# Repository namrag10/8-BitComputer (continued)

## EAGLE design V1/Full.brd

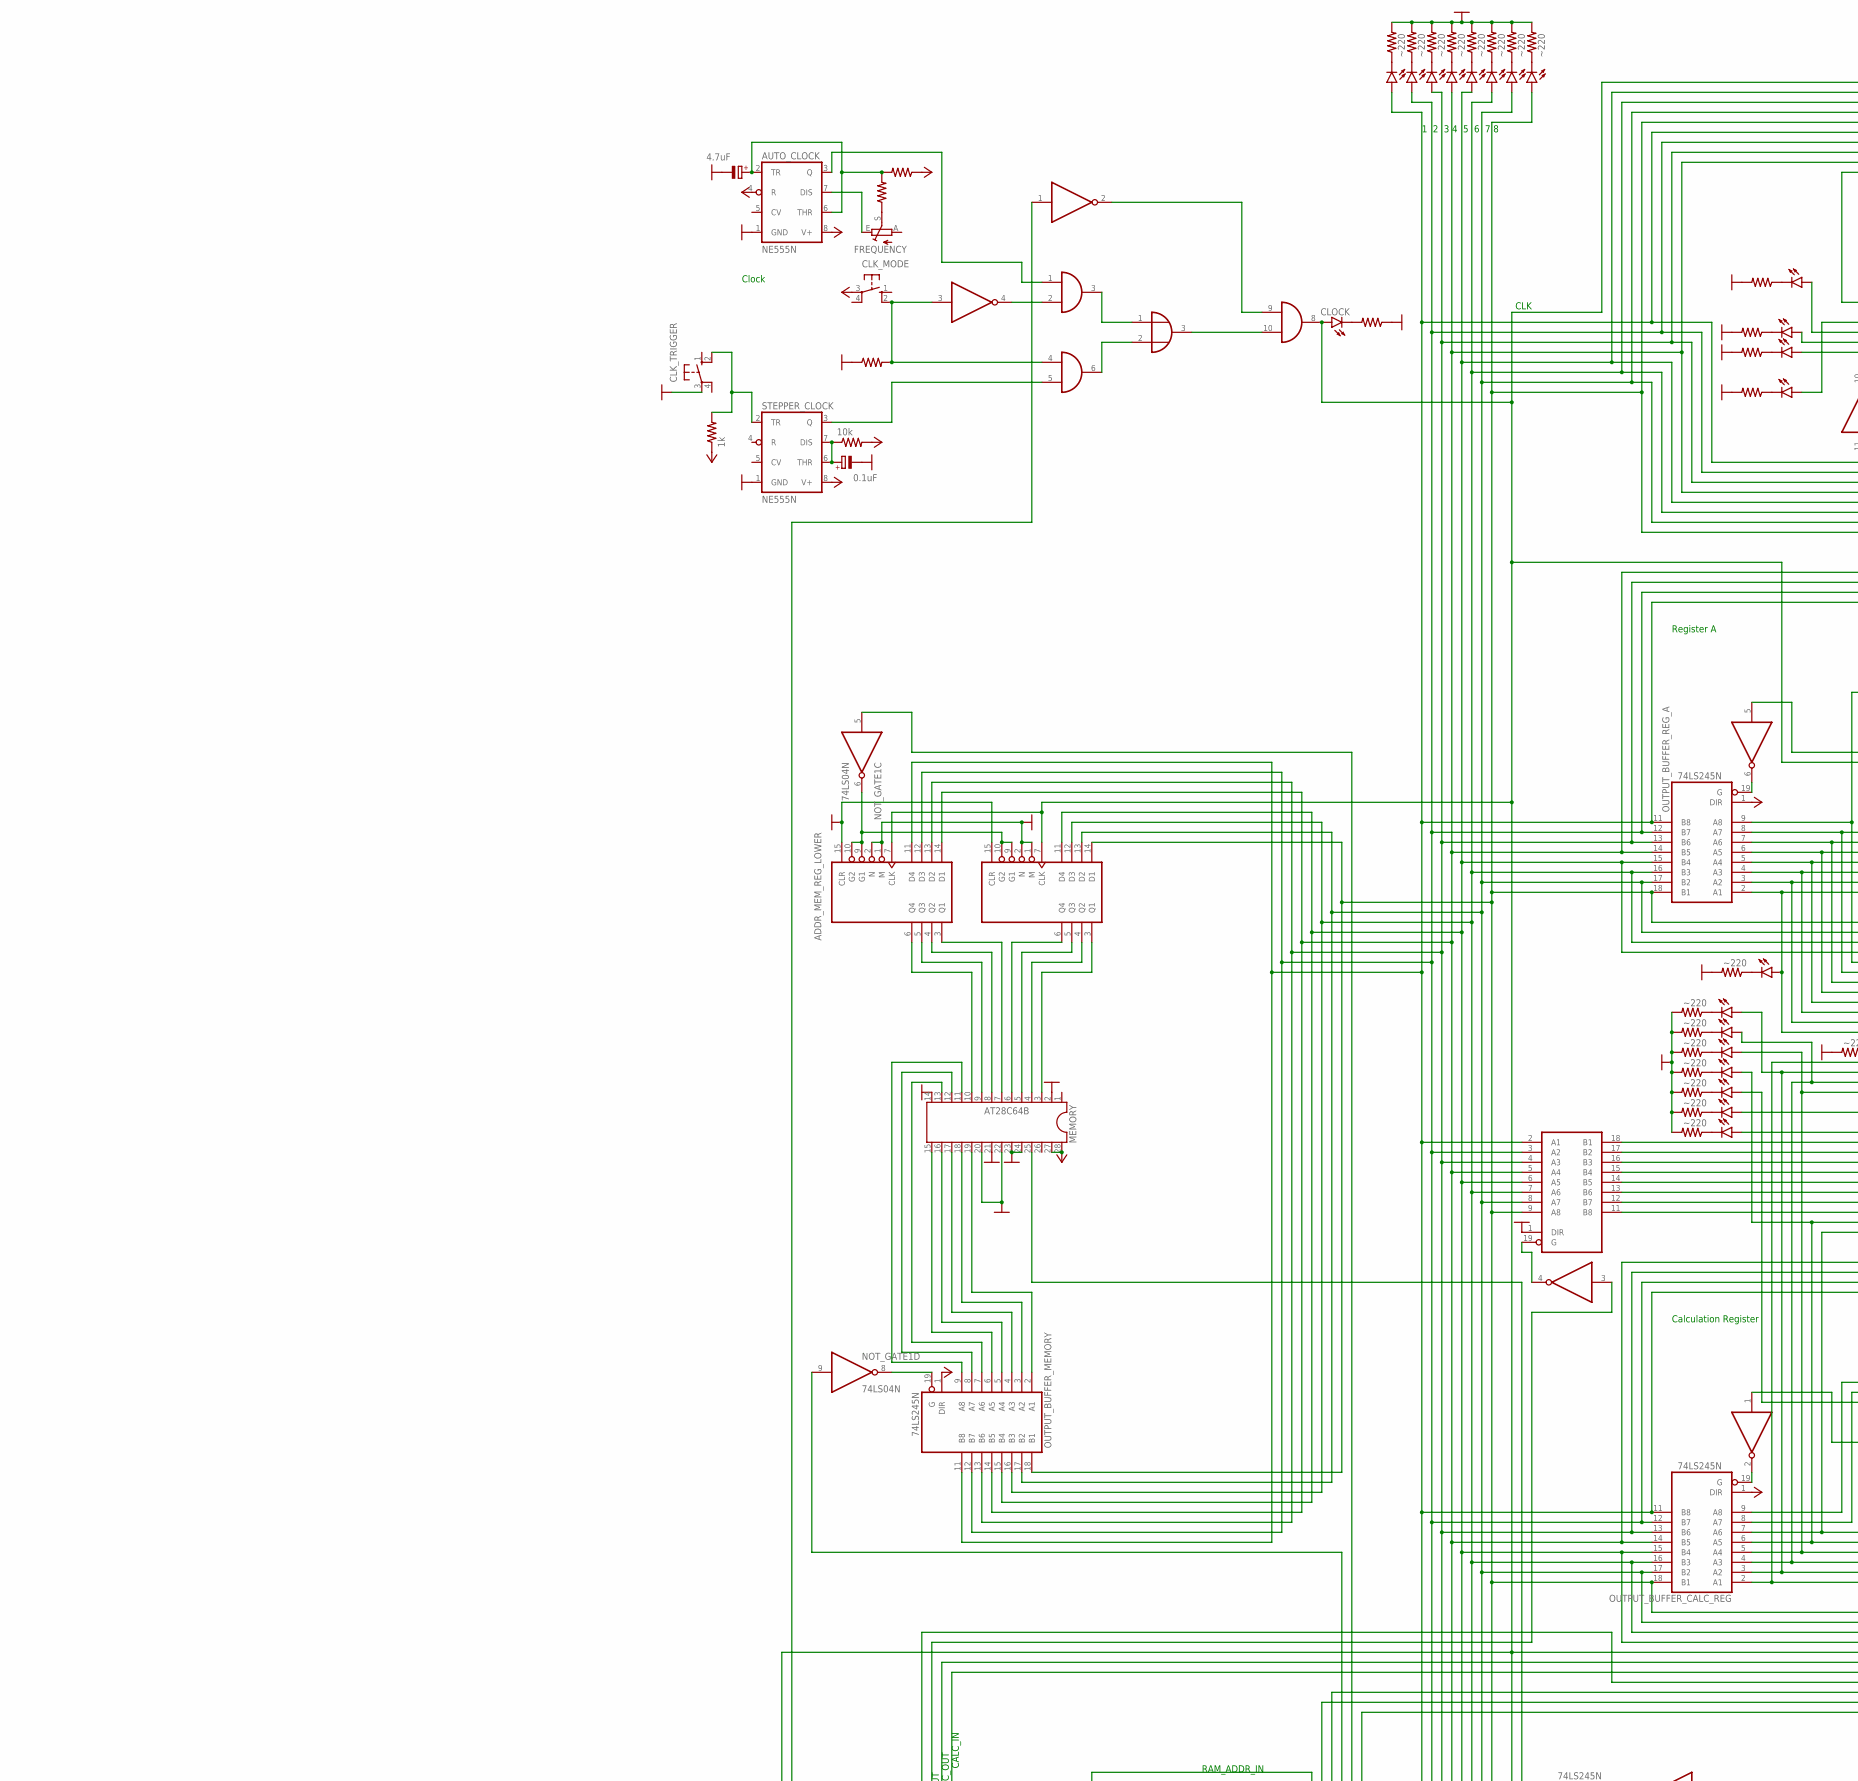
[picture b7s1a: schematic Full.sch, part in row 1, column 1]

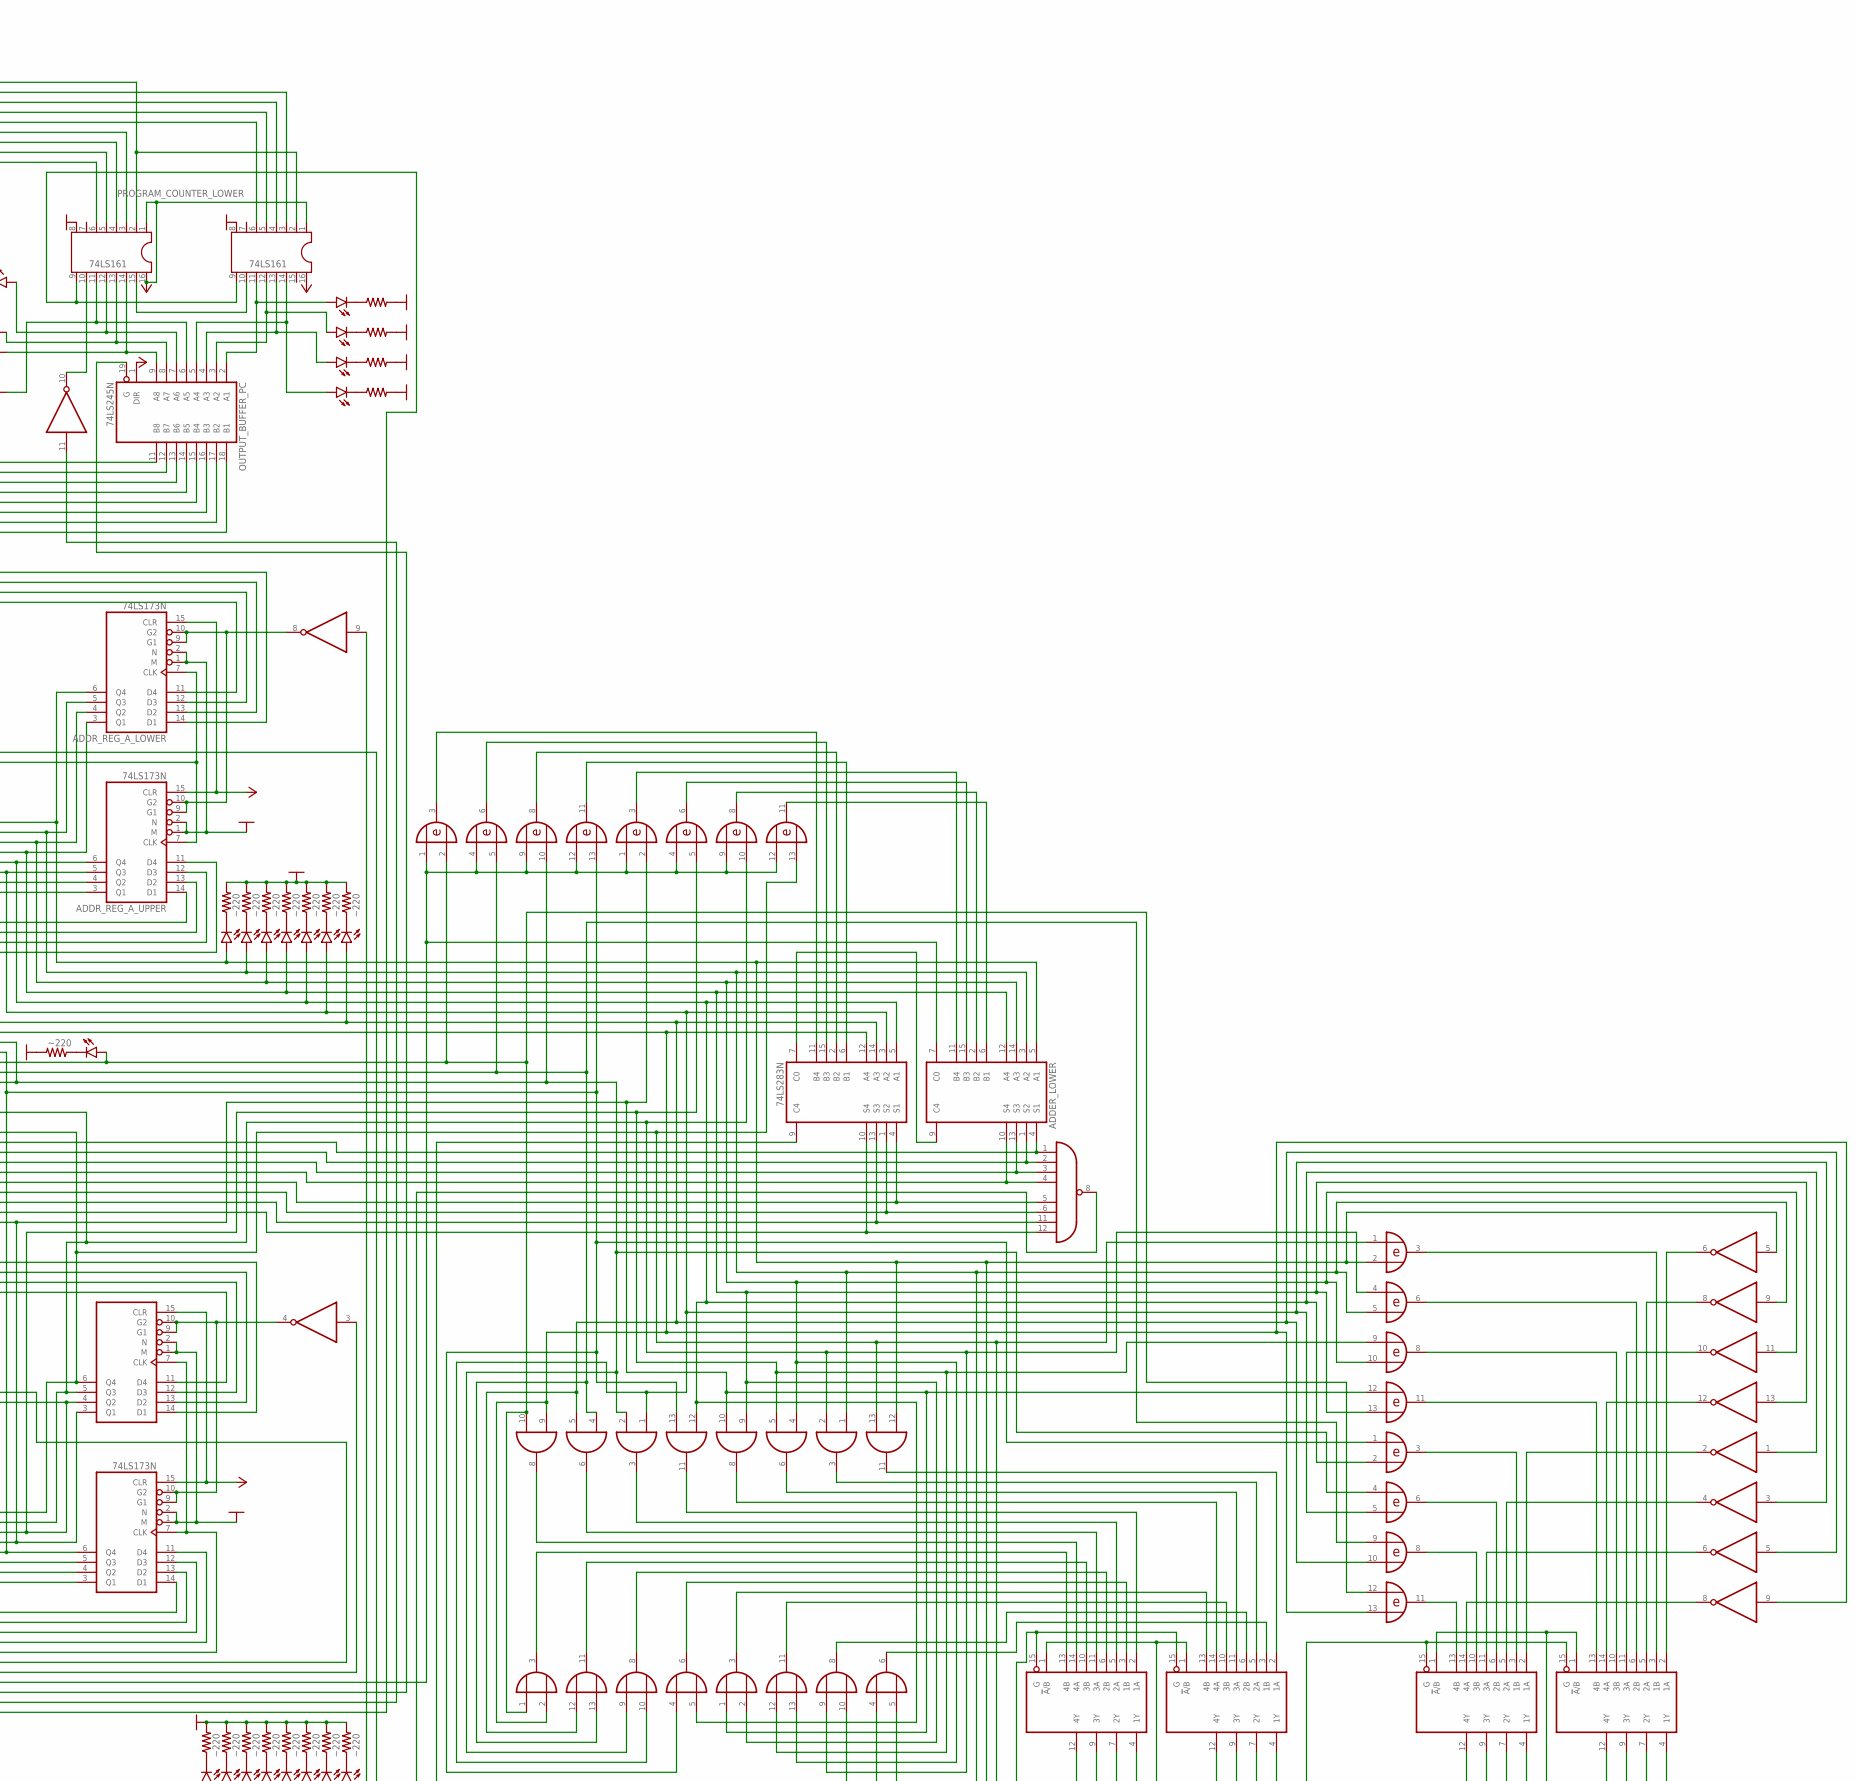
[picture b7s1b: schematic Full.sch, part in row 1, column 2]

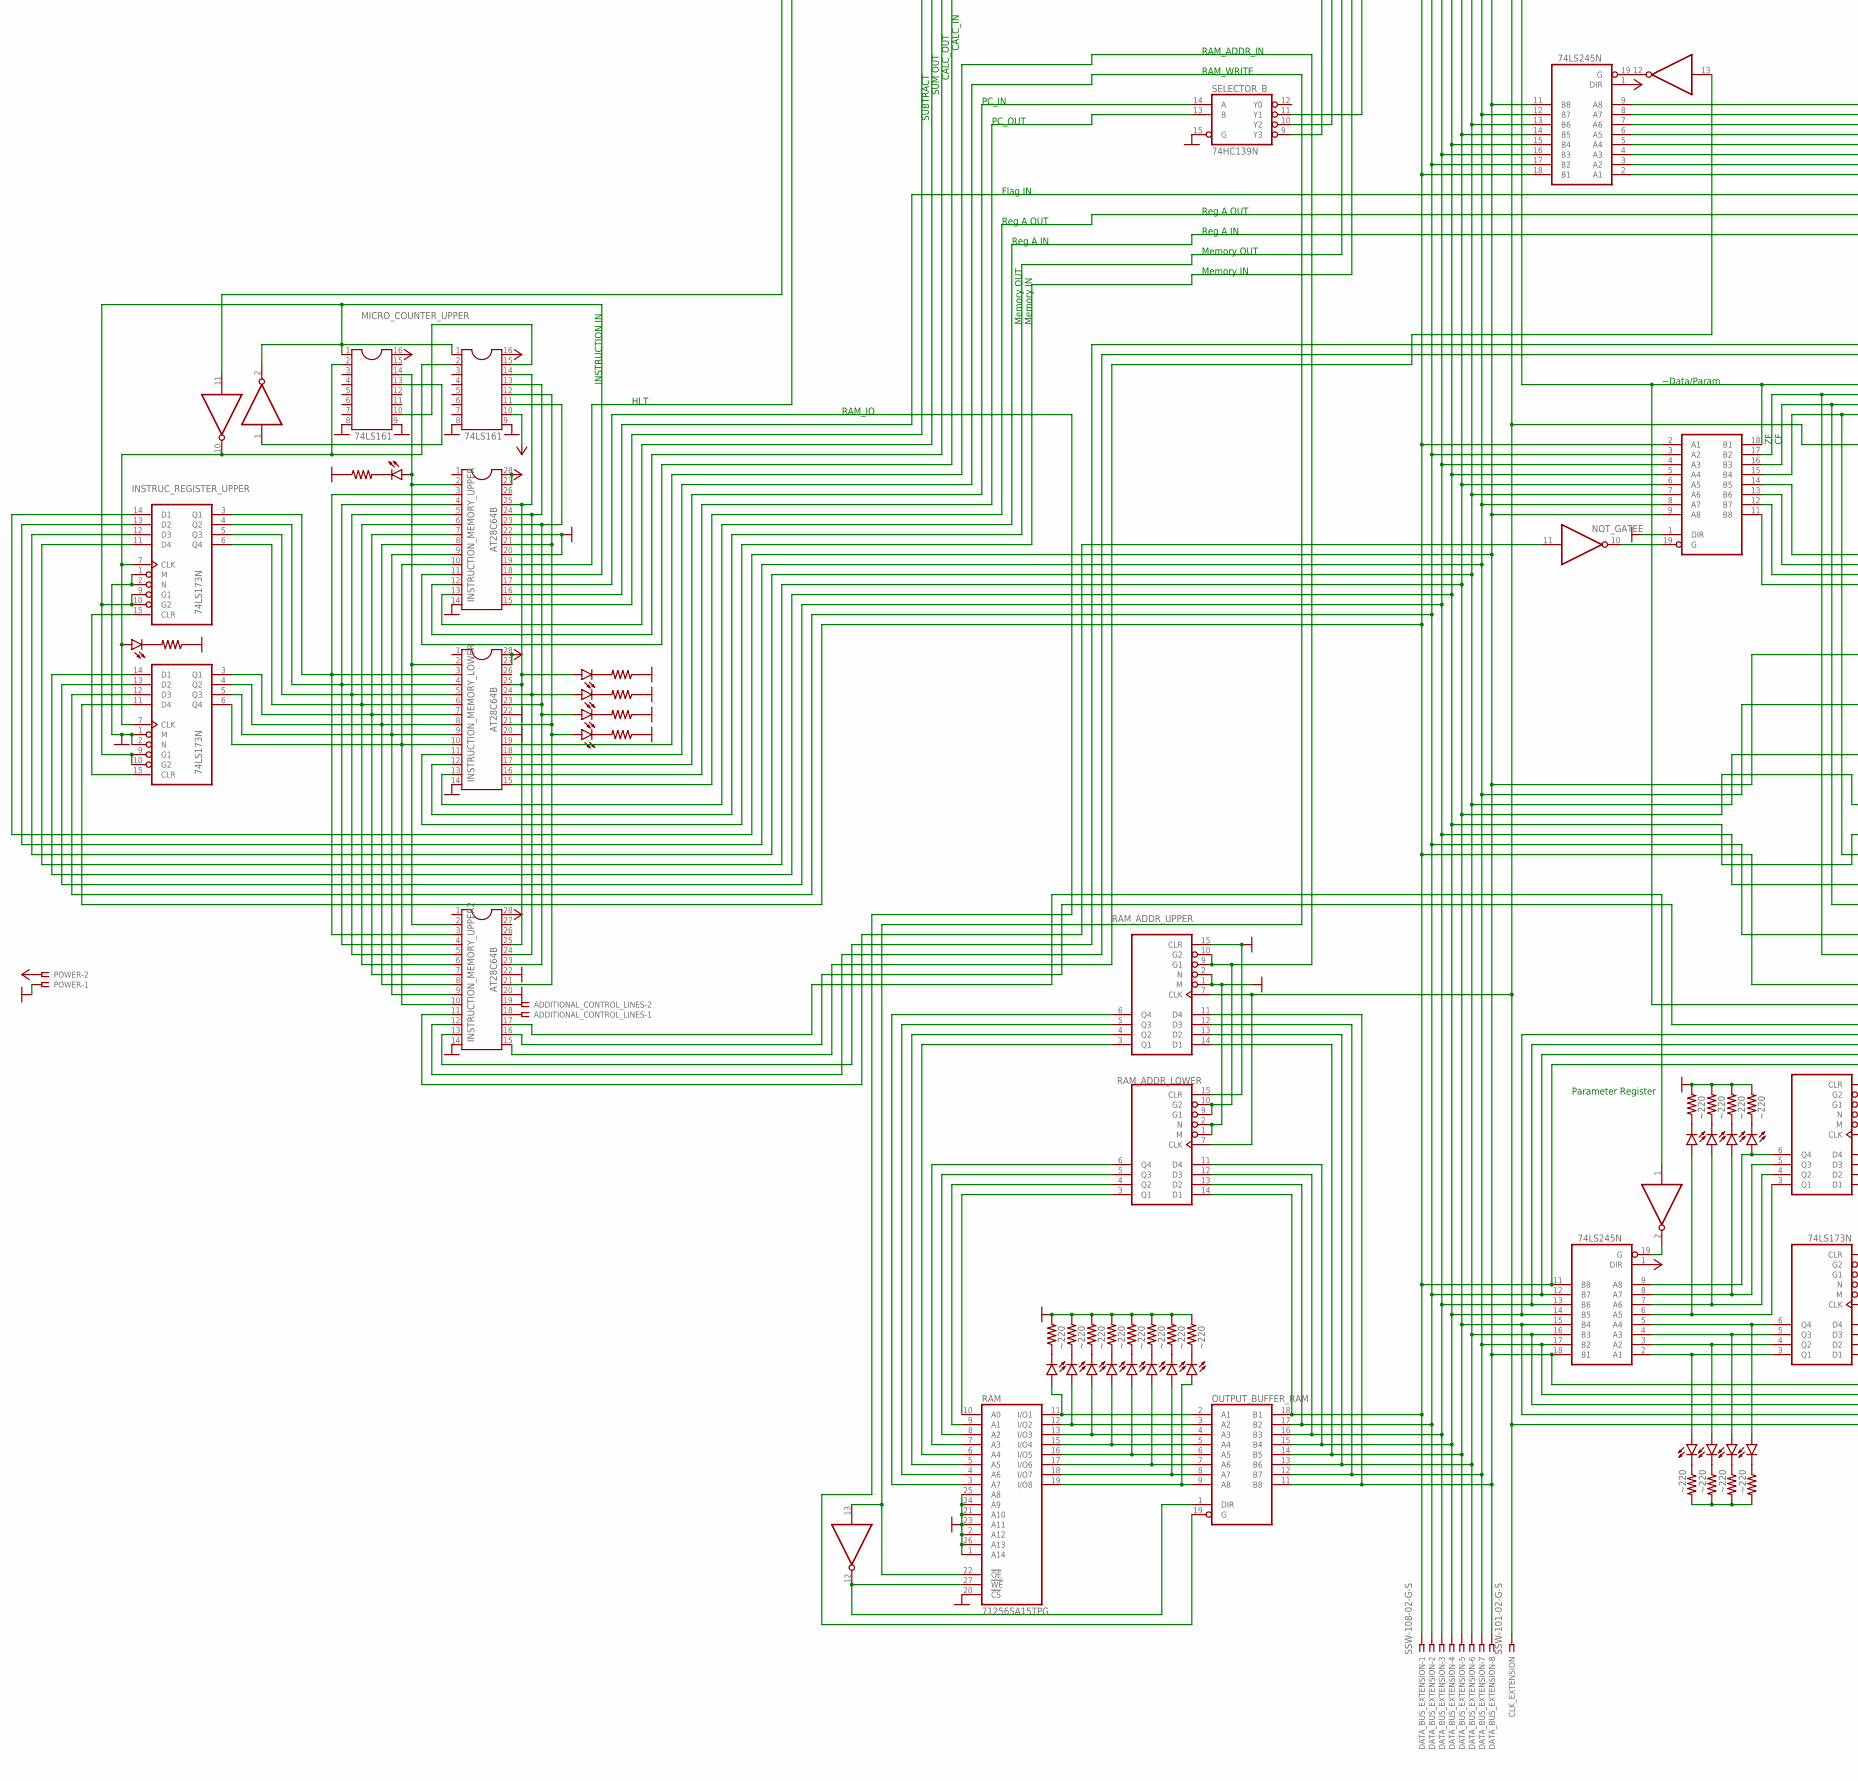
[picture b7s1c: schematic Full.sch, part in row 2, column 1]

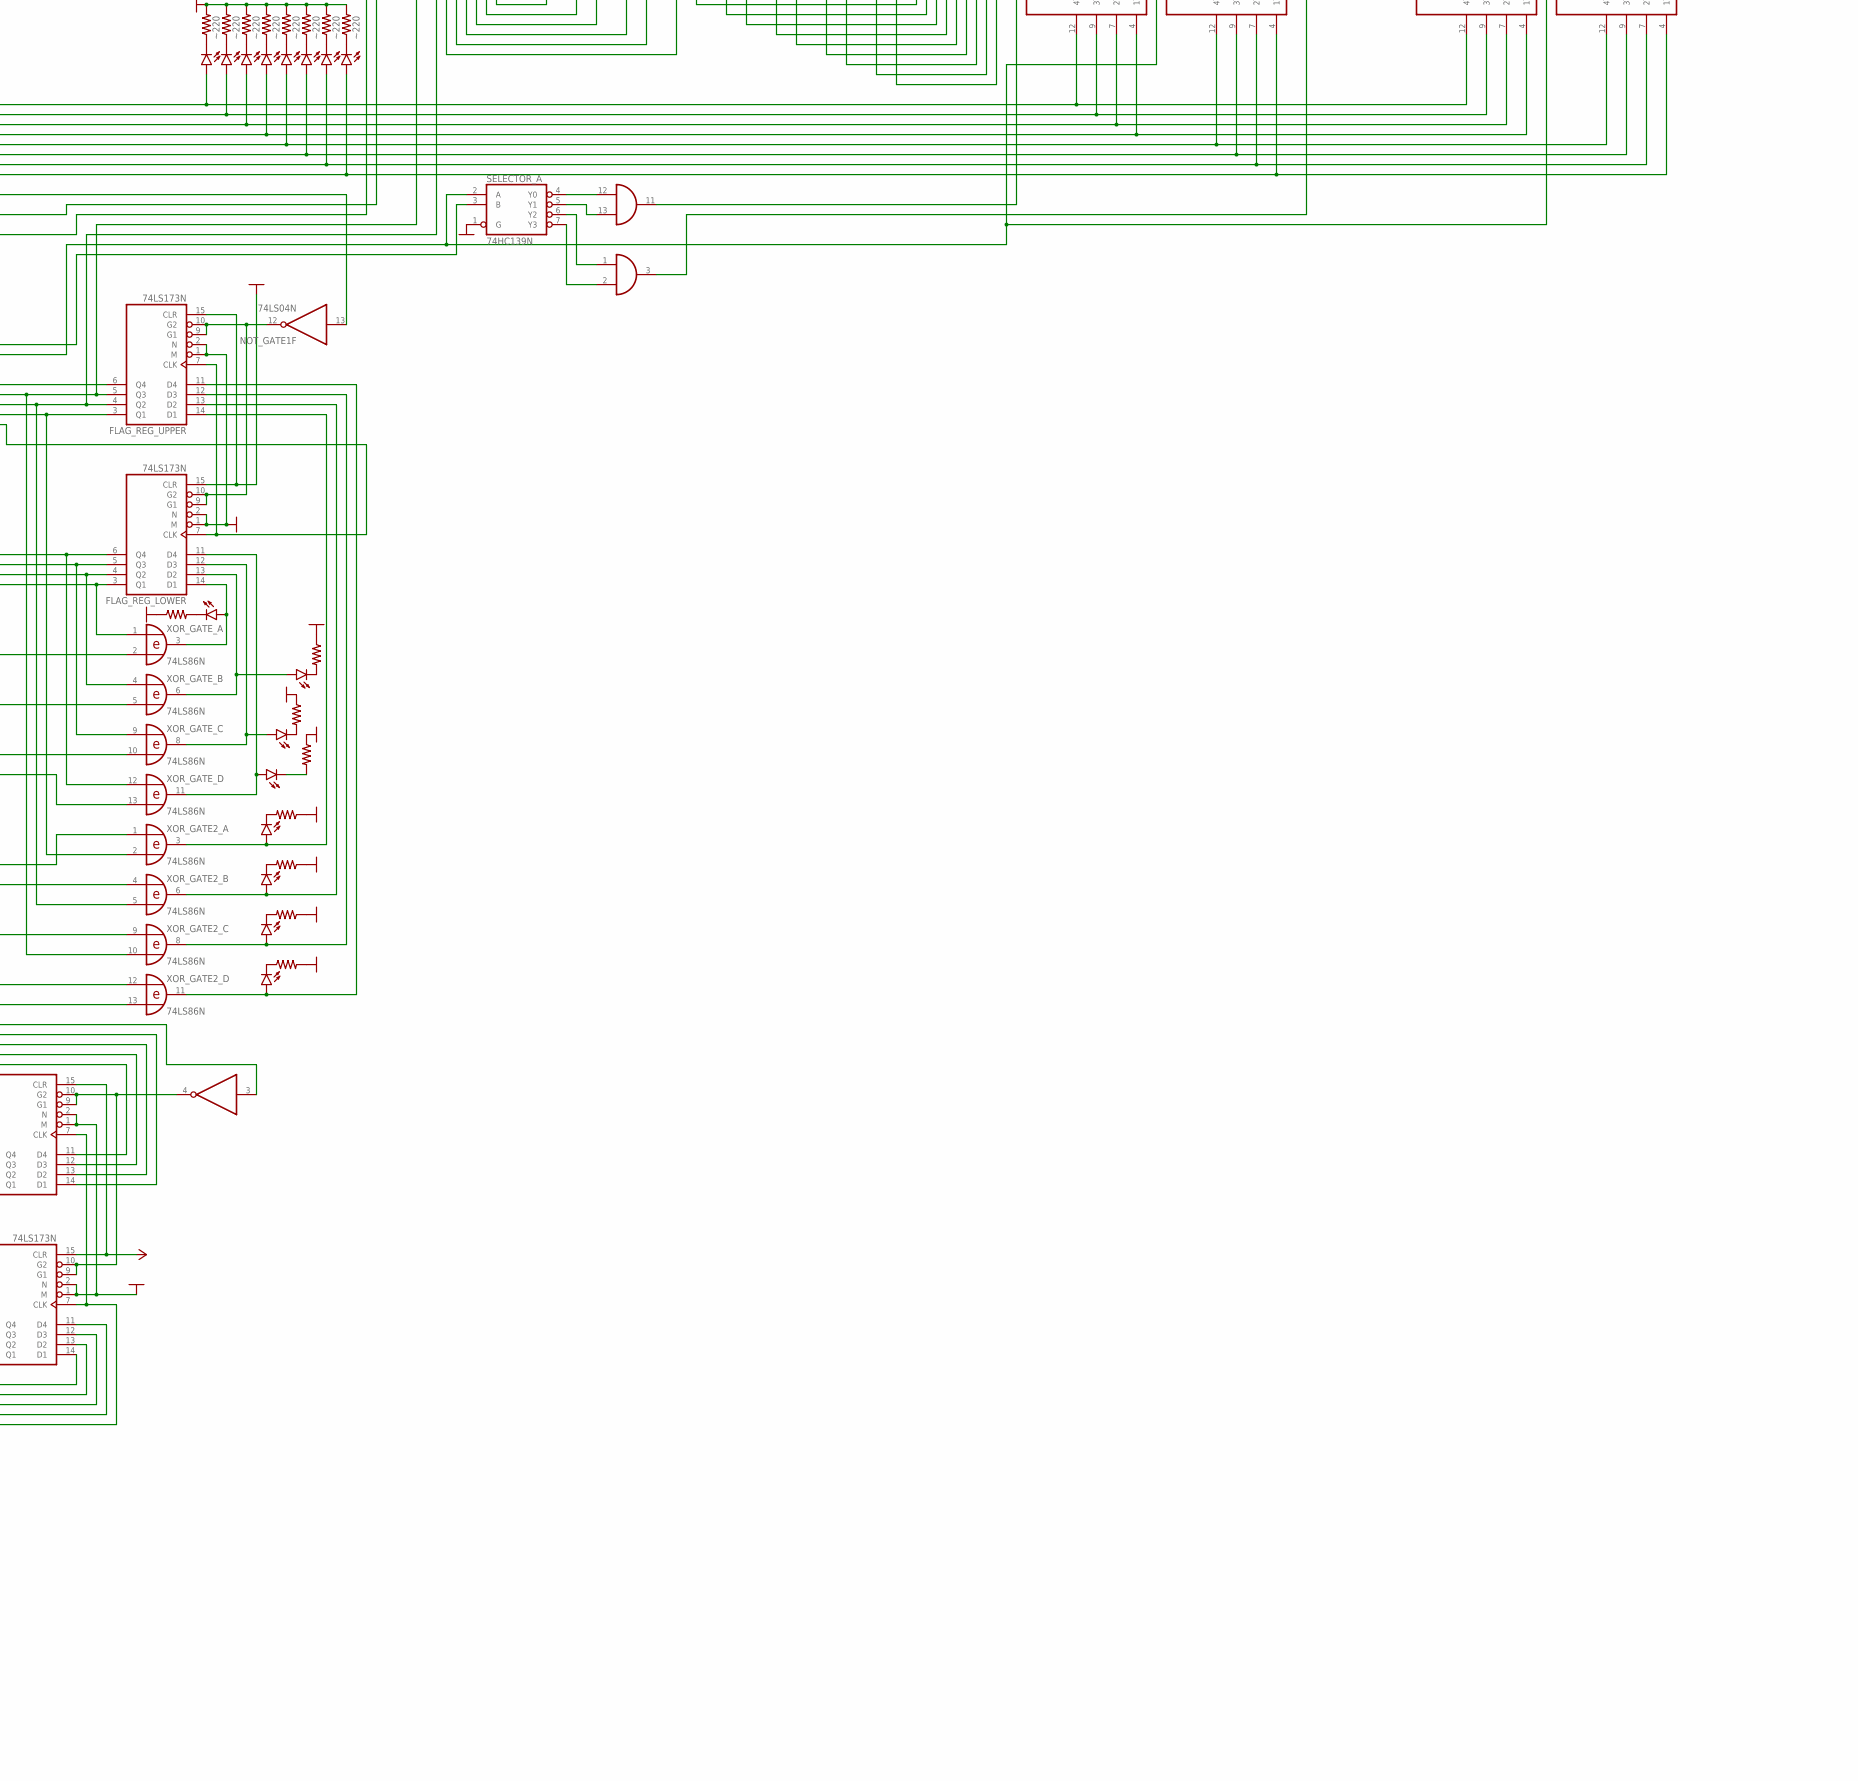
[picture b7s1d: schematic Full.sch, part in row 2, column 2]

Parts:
ADDER_LOWER: 74LS283N; DIL16
ADDER_UPPER: 74LS283N; DIL16
ADDITIONAL_CONTROL_LINES: SSW-102-02-G-S
ADDR_MEM_REG_LOWER: 74LS173N; DIL16
ADDR_MEM_REG_UPPER: 74LS173N; DIL16
ADDR_REG_A_LOWER: 74LS173N; DIL16
ADDR_REG_A_UPPER: 74LS173N; DIL16
ADDR_REG_CALC_LOWER, ADDR_REG_CALC_LOWER1: 74LS173N; DIL16
ADDR_REG_CALC_UPPER: 74LS173N; DIL16
ADDR_REG_PARAM_UPPER: 74LS173N; DIL16
AND_GATE1: 74LS30N; DIL14
AND_GATE1_, AND_GATE2_, AND_GATE3_: 74LS08N; DIL14
AND_GATE_: 74LS08N; DIL14
AUTO_CLOCK: NE555N; DIL08
C1: 4.7uF; E2-5
C2: 0.1uF; E2-5
CLK_EXTENSION: SSW-101-02-G-S
CLK_MODE: 10-XX; B3F-10XX
CLK_TRIGGER: 10-XX; B3F-10XX
CLOCK: LED5MM
DATABUS_1, DATABUS_2, DATABUS_3, DATABUS_4, DATABUS_5, DATABUS_6, DATABUS_7, DATABUS_8: LED5MM
DATA_BUS_EXTENSION: SSW-108-02-G-S
FLAG_1, FLAG_2, FLAG_3, FLAG_4, FLAG_5, FLAG_6, FLAG_7, FLAG_8: LED5MM
FLAG_REG_LOWER: 74LS173N; DIL16
FLAG_REG_UPPER: 74LS173N; DIL16
FREQUENCY: 100k; RJ9W
INSTRUCTION_MEMORY_LOWER: AT28C64B; DIL28-6
INSTRUCTION_MEMORY_UPPER, INSTRUCTION_MEMORY_UPPER2: AT28C64B; DIL28-6
INSTRUC_REGISTER_LOWER: 74LS173N; DIL16
INSTRUC_REGISTER_UPPER: 74LS173N; DIL16
INVERTED_CLK_LED: LED5MM
LED_A_REG_1, LED_A_REG_2, LED_A_REG_3, LED_A_REG_4, LED_A_REG_5, LED_A_REG_6, LED_A_REG_7, LED_A_REG_8: LED5MM
LED_B_REG_1, LED_B_REG_2, LED_B_REG_3, LED_B_REG_4, LED_B_REG_5, LED_B_REG_6, LED_B_REG_7, LED_B_REG_8: LED5MM
LOGIC_LED_1, LOGIC_LED_2, LOGIC_LED_3, LOGIC_LED_4, LOGIC_LED_5, LOGIC_LED_6, LOGIC_LED_7, LOGIC_LED_8: LED3MM
LOGIC_SELECTOR-AND/OR_LOWER: 74LS157N; DIL16
LOGIC_SELECTOR-AND/OR_UPPER: 74LS157N; DIL16
LOGIC_SELECTOR-XOR/NOT_LOWER: 74LS157N; DIL16
LOGIC_SELECTOR-XOR/NOT_UPPER: 74LS157N; DIL16
MEMORY: AT28C64B; DIL28-6
MICRO_COUNTER_LOWER: 74LS161; DIL16
MICRO_COUNTER_UPPER: 74LS161; DIL16
NOT_GATE, NOT_GATE1, NOT_GATE2_, NOT_GATE2_1, NOT_GATE3_: 74LS04N; DIL14
OR_GATE, OR_GATE1: 74LS32N; DIL14
OR_GATE_2: 74LS32N; DIL14
OUTPUT_BUFFER_ALU: 74LS245N; DIL20
OUTPUT_BUFFER_CALC_REG: 74LS245N; DIL20
OUTPUT_BUFFER_FLAGS: 74HC245N; DIL20
OUTPUT_BUFFER_LOGIC: 74LS245N; DIL20
OUTPUT_BUFFER_MEMORY: 74LS245N; DIL20
OUTPUT_BUFFER_PARAM_REG: 74LS245N; DIL20
OUTPUT_BUFFER_PC: 74LS245N; DIL20
OUTPUT_BUFFER_RAM: 74HC245N; DIL20
OUTPUT_BUFFER_REG_A: 74LS245N; DIL20
PARAM_LED_1, PARAM_LED_2, PARAM_LED_3, PARAM_LED_4, PARAM_LED_5, PARAM_LED_6, PARAM_LED_7, PARAM_LED_8: LED3MM
PC_1, PC_2, PC_3, PC_4, PC_5, PC_6, PC_7, PC_8: LED5MM
POWER: SSW-102-02-G-S
PROGRAM_COUNTER_LOWER: 74LS161; DIL16
PROGRAM_COUNTER_UPPER: 74LS161; DIL16
R1, R2: 1k; 0204/7
R3: 10k; 0204/7
R4, R7: 220; 0204/7
R5, R6, R8, R9, R10, R11, R12, R13, R14, R15, R16, R17, R18, R19, R20, R21, R22, R23, R24, R25, R26, R27, R28, R29, R30, R31, R32, R33, R34, R35, R36, R37, R38, R39, R40, R41, R42, R43, R44, R45, R46, R47, R48, R49, R50, R51, R52, R53, R54, R55, R56, R57, R58, R59, R60, R61, R62, R63, R64, R65, R66, R67, R68, R69, R70, R71, R72, R73, R74, R75, R76: ~220; 0204/7
RAM: 71256SA15TPG; DIL28-6
RAM_ADDR_LOWER: 74LS173N; DIL16
RAM_ADDR_UPPER: 74LS173N; DIL16
RAM_LED_1, RAM_LED_2, RAM_LED_3, RAM_LED_4, RAM_LED_5, RAM_LED_6, RAM_LED_7, RAM_LED_8: LED3MM
SELECTOR_: 74HC139N; DIL16
STEPPER_CLOCK: NE555N; DIL08
SUBTRACT_INVRTR_LOWER_, SUBTRACT_INVRTR_LOWER_1: 74LS86N; DIL14
SUBTRACT_INVRTR_UPPER_, SUBTRACT_INVRTR_UPPER_1: 74LS86N; DIL14
USTEP_1, USTEP_2, USTEP_3, USTEP_4, USTEP_5: LED5MM
XOR_GATE2_: 74LS86N; DIL14
XOR_GATE_: 74LS86N; DIL14

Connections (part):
1_PLACE: ADDR_MEM_REG_LOWER.11 (D4), ADDR_REG_A_LOWER.11 (D4), ADDR_REG_CALC_LOWER.11 (D4), ADDR_REG_CALC_LOWER1.11 (D4), DATABUS_1.A, DATA_BUS_EXTENSION.1, INSTRUC_REGISTER_LOWER.11 (D4), OUTPUT_BUFFER_ALU.2 (A1), OUTPUT_BUFFER_CALC_REG.11 (B8), OUTPUT_BUFFER_FLAGS.2 (A1), OUTPUT_BUFFER_LOGIC.18 (B1), OUTPUT_BUFFER_MEMORY.11 (B8), OUTPUT_BUFFER_PARAM_REG.11 (B8), OUTPUT_BUFFER_PC.11 (B8), OUTPUT_BUFFER_RAM.18 (B1), OUTPUT_BUFFER_REG_A.11 (B8), PROGRAM_COUNTER_LOWER.3, RAM_ADDR_LOWER.14 (D1), XOR_GATE2_.12 (I0)
2_PLACE: ADDR_MEM_REG_LOWER.12 (D3), ADDR_REG_A_LOWER.12 (D3), ADDR_REG_CALC_LOWER.12 (D3), ADDR_REG_CALC_LOWER1.12 (D3), DATABUS_2.A, DATA_BUS_EXTENSION.2, INSTRUC_REGISTER_LOWER.12 (D3), OUTPUT_BUFFER_ALU.3 (A2), OUTPUT_BUFFER_CALC_REG.12 (B7), OUTPUT_BUFFER_FLAGS.3 (A2), OUTPUT_BUFFER_LOGIC.17 (B2), OUTPUT_BUFFER_MEMORY.12 (B7), OUTPUT_BUFFER_PARAM_REG.12 (B7), OUTPUT_BUFFER_PC.12 (B7), OUTPUT_BUFFER_RAM.17 (B2), OUTPUT_BUFFER_REG_A.12 (B7), PROGRAM_COUNTER_LOWER.4, RAM_ADDR_LOWER.13 (D2), XOR_GATE2_.9 (I0)
4_PLACE: ADDR_MEM_REG_LOWER.13 (D2), ADDR_REG_A_LOWER.13 (D2), ADDR_REG_CALC_LOWER.13 (D2), ADDR_REG_CALC_LOWER1.13 (D2), DATABUS_3.A, DATA_BUS_EXTENSION.3, INSTRUC_REGISTER_LOWER.13 (D2), OUTPUT_BUFFER_ALU.4 (A3), OUTPUT_BUFFER_CALC_REG.13 (B6), OUTPUT_BUFFER_FLAGS.4 (A3), OUTPUT_BUFFER_LOGIC.16 (B3), OUTPUT_BUFFER_MEMORY.13 (B6), OUTPUT_BUFFER_PARAM_REG.13 (B6), OUTPUT_BUFFER_PC.13 (B6), OUTPUT_BUFFER_RAM.16 (B3), OUTPUT_BUFFER_REG_A.13 (B6), PROGRAM_COUNTER_LOWER.5, RAM_ADDR_LOWER.12 (D3), XOR_GATE2_.4 (I0)
8_PLACE: ADDR_MEM_REG_LOWER.14 (D1), ADDR_REG_A_LOWER.14 (D1), ADDR_REG_CALC_LOWER.14 (D1), ADDR_REG_CALC_LOWER1.14 (D1), DATABUS_4.A, DATA_BUS_EXTENSION.4, INSTRUC_REGISTER_LOWER.14 (D1), OUTPUT_BUFFER_ALU.5 (A4), OUTPUT_BUFFER_CALC_REG.14 (B5), OUTPUT_BUFFER_FLAGS.5 (A4), OUTPUT_BUFFER_LOGIC.15 (B4), OUTPUT_BUFFER_MEMORY.14 (B5), OUTPUT_BUFFER_PARAM_REG.14 (B5), OUTPUT_BUFFER_PC.14 (B5), OUTPUT_BUFFER_RAM.15 (B4), OUTPUT_BUFFER_REG_A.14 (B5), PROGRAM_COUNTER_LOWER.6, RAM_ADDR_LOWER.11 (D4), XOR_GATE2_.1 (I0)
16_PLACE: ADDR_MEM_REG_UPPER.11 (D4), ADDR_REG_A_UPPER.11 (D4), ADDR_REG_CALC_UPPER.11 (D4), ADDR_REG_PARAM_UPPER.11 (D4), DATABUS_5.A, DATA_BUS_EXTENSION.5, INSTRUC_REGISTER_UPPER.11 (D4), OUTPUT_BUFFER_ALU.6 (A5), OUTPUT_BUFFER_CALC_REG.15 (B4), OUTPUT_BUFFER_FLAGS.6 (A5), OUTPUT_BUFFER_LOGIC.14 (B5), OUTPUT_BUFFER_MEMORY.15 (B4), OUTPUT_BUFFER_PARAM_REG.15 (B4), OUTPUT_BUFFER_PC.15 (B4), OUTPUT_BUFFER_RAM.14 (B5), OUTPUT_BUFFER_REG_A.15 (B4), PROGRAM_COUNTER_UPPER.3, RAM_ADDR_UPPER.14 (D1), XOR_GATE_.13 (I1)
32_PLACE: ADDR_MEM_REG_UPPER.12 (D3), ADDR_REG_A_UPPER.12 (D3), ADDR_REG_CALC_UPPER.12 (D3), ADDR_REG_PARAM_UPPER.12 (D3), DATABUS_6.A, DATA_BUS_EXTENSION.6, INSTRUC_REGISTER_UPPER.12 (D3), OUTPUT_BUFFER_ALU.7 (A6), OUTPUT_BUFFER_CALC_REG.16 (B3), OUTPUT_BUFFER_FLAGS.7 (A6), OUTPUT_BUFFER_LOGIC.13 (B6), OUTPUT_BUFFER_MEMORY.16 (B3), OUTPUT_BUFFER_PARAM_REG.16 (B3), OUTPUT_BUFFER_PC.16 (B3), OUTPUT_BUFFER_RAM.13 (B6), OUTPUT_BUFFER_REG_A.16 (B3), PROGRAM_COUNTER_UPPER.4, RAM_ADDR_UPPER.13 (D2), XOR_GATE_.10 (I1)
64_PLACE: ADDR_MEM_REG_UPPER.13 (D2), ADDR_REG_A_UPPER.13 (D2), ADDR_REG_CALC_UPPER.13 (D2), ADDR_REG_PARAM_UPPER.13 (D2), DATABUS_7.A, DATA_BUS_EXTENSION.7, INSTRUC_REGISTER_UPPER.13 (D2), OUTPUT_BUFFER_ALU.8 (A7), OUTPUT_BUFFER_CALC_REG.17 (B2), OUTPUT_BUFFER_FLAGS.8 (A7), OUTPUT_BUFFER_LOGIC.12 (B7), OUTPUT_BUFFER_MEMORY.17 (B2), OUTPUT_BUFFER_PARAM_REG.17 (B2), OUTPUT_BUFFER_PC.17 (B2), OUTPUT_BUFFER_RAM.12 (B7), OUTPUT_BUFFER_REG_A.17 (B2), PROGRAM_COUNTER_UPPER.5, RAM_ADDR_UPPER.12 (D3), XOR_GATE_.5 (I1)
128_PLACE: ADDR_MEM_REG_UPPER.14 (D1), ADDR_REG_A_UPPER.14 (D1), ADDR_REG_CALC_UPPER.14 (D1), ADDR_REG_PARAM_UPPER.14 (D1), DATABUS_8.A, DATA_BUS_EXTENSION.8, INSTRUC_REGISTER_UPPER.14 (D1), OUTPUT_BUFFER_ALU.9 (A8), OUTPUT_BUFFER_CALC_REG.18 (B1), OUTPUT_BUFFER_FLAGS.9 (A8), OUTPUT_BUFFER_LOGIC.11 (B8), OUTPUT_BUFFER_MEMORY.18 (B1), OUTPUT_BUFFER_PARAM_REG.18 (B1), OUTPUT_BUFFER_PC.18 (B1), OUTPUT_BUFFER_RAM.11 (B8), OUTPUT_BUFFER_REG_A.18 (B1), PROGRAM_COUNTER_UPPER.6, RAM_ADDR_UPPER.11 (D4), XOR_GATE_.2 (I1)
+5V: AUTO_CLOCK.4 (R), AUTO_CLOCK.8 (V+), CLK_MODE.3, R1.1, R2.1, R3.2, STEPPER_CLOCK.8 (V+)
CLOCK: ADDR_MEM_REG_LOWER.7 (CLK), ADDR_MEM_REG_UPPER.7 (CLK), ADDR_REG_A_LOWER.7 (CLK), ADDR_REG_A_UPPER.7 (CLK), ADDR_REG_CALC_LOWER.7 (CLK), ADDR_REG_CALC_LOWER1.7 (CLK), ADDR_REG_CALC_UPPER.7 (CLK), ADDR_REG_PARAM_UPPER.7 (CLK), AND_GATE_.8 (O), CLK_EXTENSION.1, CLOCK.A, FLAG_REG_LOWER.7 (CLK), FLAG_REG_UPPER.7 (CLK), NOT_GATE1.11 (I), PROGRAM_COUNTER_LOWER.2, PROGRAM_COUNTER_UPPER.2, RAM_ADDR_LOWER.7 (CLK), RAM_ADDR_UPPER.7 (CLK)
CTRL_SIG_5: INSTRUCTION_MEMORY_LOWER.16, SELECTOR_.13 (B)
CTRL_SIG_6: INSTRUCTION_MEMORY_LOWER.17, SELECTOR_.14 (A)
CTRL_SIG_9_(CALC_REG_IN): INSTRUCTION_MEMORY_UPPER.11, NOT_GATE2_.3 (I)
CTRL_SIG_10_(CALC_REG_OUT): INSTRUCTION_MEMORY_UPPER.12, NOT_GATE2_.1 (I)
CTRL_SIG_11_(SUM_OUT): INSTRUCTION_MEMORY_UPPER.13, NOT_GATE3_.3 (I)
CTRL_SIG_12_(SUBTRACT): ADDER_LOWER.7 (C0), INSTRUCTION_MEMORY_UPPER.15, SUBTRACT_INVRTR_LOWER_.1 (I0), SUBTRACT_INVRTR_LOWER_.4 (I0), SUBTRACT_INVRTR_LOWER_.9 (I0), SUBTRACT_INVRTR_LOWER_.12 (I0), SUBTRACT_INVRTR_UPPER_.1 (I0), SUBTRACT_INVRTR_UPPER_.4 (I0), SUBTRACT_INVRTR_UPPER_.9 (I0), SUBTRACT_INVRTR_UPPER_.12 (I0)
FLAG_OUT: INSTRUCTION_MEMORY_UPPER2.11, NOT_GATE.11 (I)
FLAG_TOGGLE_IN: INSTRUCTION_MEMORY_UPPER.16, NOT_GATE1.13 (I)
GND: ADDER_LOWER.8 (GND), ADDER_UPPER.8 (GND), ADDR_MEM_REG_LOWER.1 (M), ADDR_MEM_REG_LOWER.2 (N), ADDR_MEM_REG_LOWER.8 (GND), ADDR_MEM_REG_LOWER.15 (CLR), ADDR_MEM_REG_UPPER.1 (M), ADDR_MEM_REG_UPPER.2 (N), ADDR_MEM_REG_UPPER.8 (GND), ADDR_MEM_REG_UPPER.15 (CLR), ADDR_REG_A_LOWER.1 (M), ADDR_REG_A_LOWER.2 (N), ADDR_REG_A_LOWER.8 (GND), ADDR_REG_A_UPPER.1 (M), ADDR_REG_A_UPPER.2 (N), ADDR_REG_A_UPPER.8 (GND), ADDR_REG_CALC_LOWER.1 (M), ADDR_REG_CALC_LOWER.2 (N), ADDR_REG_CALC_LOWER.8 (GND), ADDR_REG_CALC_LOWER1.1 (M), ADDR_REG_CALC_LOWER1.2 (N), ADDR_REG_CALC_LOWER1.8 (GND), ADDR_REG_CALC_UPPER.1 (M), ADDR_REG_CALC_UPPER.2 (N), ADDR_REG_CALC_UPPER.8 (GND), ADDR_REG_PARAM_UPPER.1 (M), ADDR_REG_PARAM_UPPER.2 (N), ADDR_REG_PARAM_UPPER.8 (GND), AND_GATE1.7 (GND), AND_GATE1_.7 (GND), AND_GATE2_.7 (GND), AND_GATE3_.7 (GND), AND_GATE_.7 (GND), AUTO_CLOCK.1 (GND), C1.-, C2.-, CLK_TRIGGER.3, FLAG_REG_LOWER.1 (M), FLAG_REG_LOWER.2 (N), FLAG_REG_LOWER.8 (GND), FLAG_REG_LOWER.15 (CLR), FLAG_REG_UPPER.1 (M), FLAG_REG_UPPER.2 (N), FLAG_REG_UPPER.8 (GND), FLAG_REG_UPPER.15 (CLR), INSTRUCTION_MEMORY_LOWER.14, INSTRUCTION_MEMORY_LOWER.20, INSTRUCTION_MEMORY_LOWER.22, INSTRUCTION_MEMORY_UPPER.14, INSTRUCTION_MEMORY_UPPER.20, INSTRUCTION_MEMORY_UPPER.22, INSTRUCTION_MEMORY_UPPER2.14, INSTRUCTION_MEMORY_UPPER2.20, INSTRUCTION_MEMORY_UPPER2.22, INSTRUC_REGISTER_LOWER.1 (M), INSTRUC_REGISTER_LOWER.2 (N), INSTRUC_REGISTER_LOWER.8 (GND), INSTRUC_REGISTER_UPPER.1 (M), INSTRUC_REGISTER_UPPER.2 (N), INSTRUC_REGISTER_UPPER.8 (GND), LOGIC_SELECTOR-AND/OR_LOWER.8 (GND), LOGIC_SELECTOR-AND/OR_UPPER.8 (GND), LOGIC_SELECTOR-XOR/NOT_LOWER.8 (GND), LOGIC_SELECTOR-XOR/NOT_UPPER.8 (GND), MEMORY.2, MEMORY.14, MEMORY.20, MEMORY.21, MEMORY.22, MEMORY.23, MEMORY.24, MICRO_COUNTER_LOWER.8, MICRO_COUNTER_LOWER.9, MICRO_COUNTER_UPPER.8, MICRO_COUNTER_UPPER.9, NOT_GATE.7 (GND), NOT_GATE1.7 (GND), NOT_GATE2_.7 (GND), NOT_GATE2_1.7 (GND), NOT_GATE3_.7 (GND), OR_GATE.7 (GND), OR_GATE1.7 (GND), OR_GATE_2.7 (GND), OUTPUT_BUFFER_ALU.1 (DIR), OUTPUT_BUFFER_ALU.10 (GND)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
HLT_SIGNAL: INSTRUCTION_MEMORY_UPPER.19, NOT_GATE1.1 (I)
INSTRUCTION_A1: INSTRUCTION_MEMORY_LOWER.10, INSTRUCTION_MEMORY_UPPER.10, INSTRUCTION_MEMORY_UPPER2.10, INSTRUC_REGISTER_LOWER.6 (Q4)
INSTRUCTION_A2: INSTRUCTION_MEMORY_LOWER.9, INSTRUCTION_MEMORY_UPPER.9, INSTRUCTION_MEMORY_UPPER2.9, INSTRUC_REGISTER_LOWER.5 (Q3)
INSTRUCTION_A3: INSTRUCTION_MEMORY_LOWER.8, INSTRUCTION_MEMORY_UPPER.8, INSTRUCTION_MEMORY_UPPER2.8, INSTRUC_REGISTER_LOWER.4 (Q2)
INSTRUCTION_A4: INSTRUCTION_MEMORY_LOWER.7, INSTRUCTION_MEMORY_UPPER.7, INSTRUCTION_MEMORY_UPPER2.7, INSTRUC_REGISTER_LOWER.3 (Q1)
INSTRUCTION_A5: INSTRUCTION_MEMORY_LOWER.5, INSTRUCTION_MEMORY_UPPER.5, INSTRUCTION_MEMORY_UPPER2.5, INSTRUC_REGISTER_UPPER.5 (Q3)
INSTRUCTION_A6: INSTRUCTION_MEMORY_LOWER.4, INSTRUCTION_MEMORY_UPPER.4, INSTRUCTION_MEMORY_UPPER2.4, INSTRUC_REGISTER_UPPER.4 (Q2)
INSTRUCTION_A7: INSTRUCTION_MEMORY_LOWER.3, INSTRUCTION_MEMORY_UPPER.3, INSTRUCTION_MEMORY_UPPER2.3, INSTRUC_REGISTER_UPPER.3 (Q1)
INSTRUCTION_REG_IN: INSTRUCTION_MEMORY_UPPER.18, INSTRUC_REGISTER_LOWER.9 (G1), INSTRUC_REGISTER_LOWER.10 (G2), INSTRUC_REGISTER_UPPER.9 (G1), INSTRUC_REGISTER_UPPER.10 (G2), MICRO_COUNTER_LOWER.1, MICRO_COUNTER_UPPER.1, NOT_GATE3_.2 (O)
INSTRUCTION__A4: INSTRUCTION_MEMORY_LOWER.6, INSTRUCTION_MEMORY_UPPER.6, INSTRUCTION_MEMORY_UPPER2.6, INSTRUC_REGISTER_UPPER.6 (Q4)
INVERTED_CLOCK: INSTRUC_REGISTER_LOWER.7 (CLK), INSTRUC_REGISTER_UPPER.7 (CLK), INVERTED_CLK_LED.A, MICRO_COUNTER_LOWER.2, MICRO_COUNTER_UPPER.2, NOT_GATE1.10 (O)
INV_HLT_SIGNAL: AND_GATE_.9 (I0), NOT_GATE1.2 (O)
LOGIC_1: LOGIC_LED_1.A, LOGIC_SELECTOR-AND/OR_LOWER.4 (1Y), LOGIC_SELECTOR-XOR/NOT_LOWER.4 (1Y), OUTPUT_BUFFER_LOGIC.2 (A1)
LOGIC_2: LOGIC_LED_2.A, LOGIC_SELECTOR-AND/OR_LOWER.7 (2Y), LOGIC_SELECTOR-XOR/NOT_LOWER.7 (2Y), OUTPUT_BUFFER_LOGIC.3 (A2)
LOGIC_3: LOGIC_LED_3.A, LOGIC_SELECTOR-AND/OR_LOWER.9 (3Y), LOGIC_SELECTOR-XOR/NOT_LOWER.9 (3Y), OUTPUT_BUFFER_LOGIC.4 (A3)
LOGIC_4: LOGIC_LED_4.A, LOGIC_SELECTOR-AND/OR_LOWER.12 (4Y), LOGIC_SELECTOR-XOR/NOT_LOWER.12 (4Y), OUTPUT_BUFFER_LOGIC.5 (A4)
LOGIC_5: LOGIC_LED_5.A, LOGIC_SELECTOR-AND/OR_UPPER.4 (1Y), LOGIC_SELECTOR-XOR/NOT_UPPER.4 (1Y), OUTPUT_BUFFER_LOGIC.6 (A5)
LOGIC_6: LOGIC_LED_6.A, LOGIC_SELECTOR-AND/OR_UPPER.7 (2Y), LOGIC_SELECTOR-XOR/NOT_UPPER.7 (2Y), OUTPUT_BUFFER_LOGIC.7 (A6)
LOGIC_7: LOGIC_LED_7.A, LOGIC_SELECTOR-AND/OR_UPPER.9 (3Y), LOGIC_SELECTOR-XOR/NOT_UPPER.9 (3Y), OUTPUT_BUFFER_LOGIC.8 (A7)
LOGIC_8: LOGIC_LED_8.A, LOGIC_SELECTOR-AND/OR_UPPER.12 (4Y), LOGIC_SELECTOR-XOR/NOT_UPPER.12 (4Y), OUTPUT_BUFFER_LOGIC.9 (A8)
LOGIC_OUT: INSTRUCTION_MEMORY_UPPER2.15, NOT_GATE.13 (I)
LOGIC_SELECT_1: INSTRUCTION_MEMORY_UPPER2.12, LOGIC_SELECTOR-AND/OR_LOWER.1 (!A!/B), LOGIC_SELECTOR-AND/OR_UPPER.1 (!A!/B), LOGIC_SELECTOR-XOR/NOT_LOWER.1 (!A!/B), LOGIC_SELECTOR-XOR/NOT_UPPER.1 (!A!/B), SELECTOR_.2 (A)
LOGIC_SELECT_2: INSTRUCTION_MEMORY_UPPER2.13, SELECTOR_.3 (B)
MEMORY_IN: INSTRUCTION_MEMORY_LOWER.11, NOT_GATE1.5 (I)
MEMORY_OUT: INSTRUCTION_MEMORY_LOWER.12, NOT_GATE1.9 (I)
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
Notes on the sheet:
Register A
Clock
1 2 3 4 5 6 7 8
Flag IN
Memory IN
Memory OUT
Calculation Register
CLK
Reg A IN
Reg A OUT
PC_IN
PC_OUT
~Data/Param
HLT
INSTRUCTION IN
CALC_IN
CALC_OUT
SUM OUT
SUBTRACT
RAM_WRITE
RAM_ADDR_IN
RAM_IO
Parameter Register

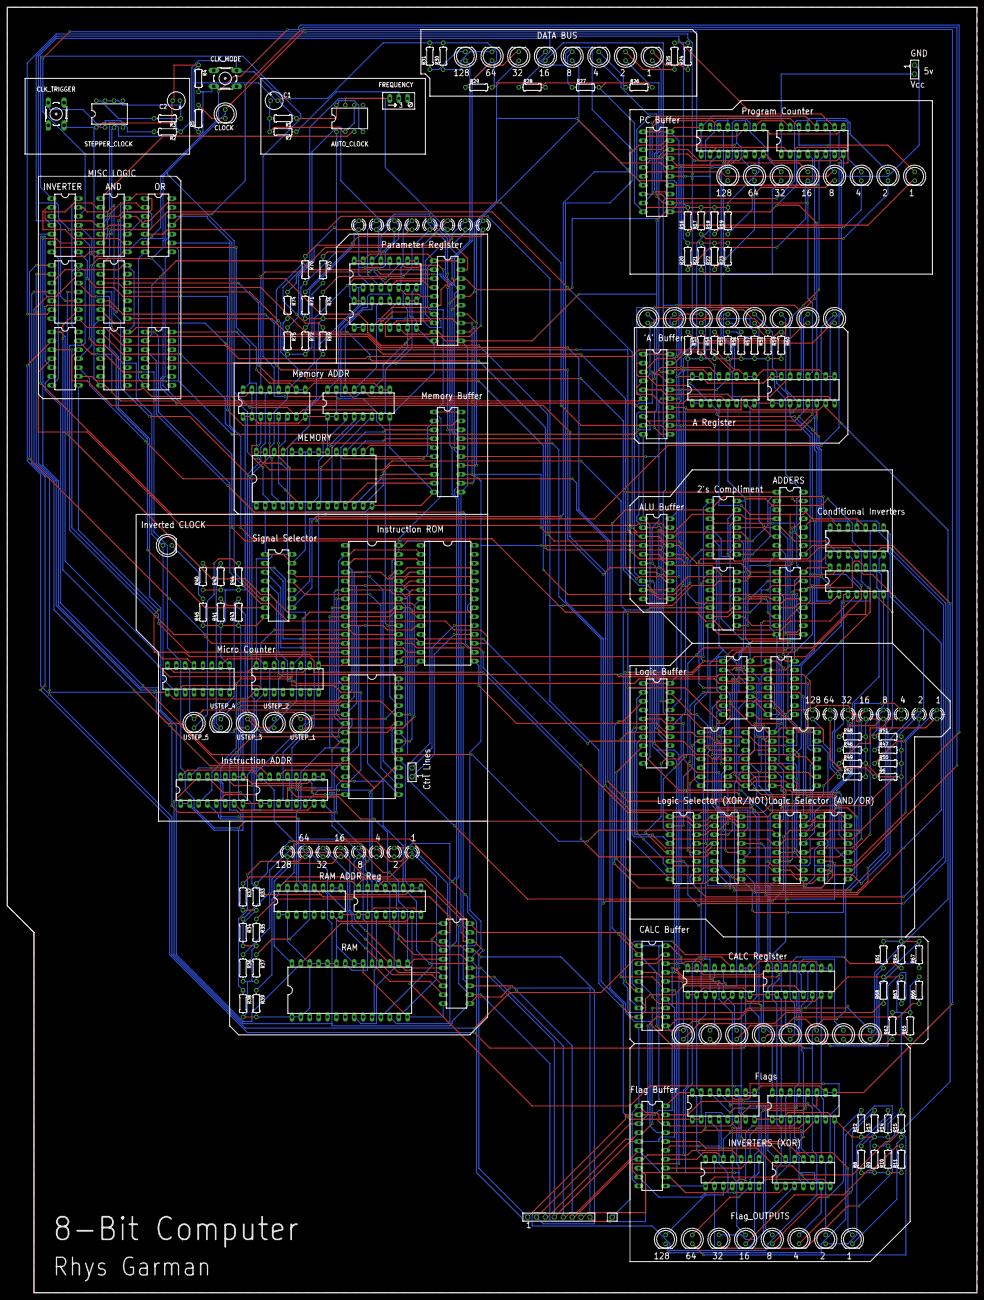
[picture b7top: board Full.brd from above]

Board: 2 copper layers, 276.9 x 367.0 mm, 216 parts (0 on the bottom side), 294 nets.
